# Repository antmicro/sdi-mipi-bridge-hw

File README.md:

# SDI to MIPI CSI-2 Bridge Hardware Design

Copyright (c) 2020-2023 [Antmicro](https://www.antmicro.com)

## Overview

This project contains open hardware KiCad design files for Antmicro's SDI to MIPI CSI-2 bridge.
This device enables connecting industrial and filmmaking cameras and video accessories to edge AI platforms which often include the MIPI CSI-2 interface.

The board includes an SDI input BNC connector and Antmicro's standard 50-pin FFC output connector (compatible with a range of our open hardware boards) exposing MIPI CSI-2 lanes as well as an I2C bus for configuration.

An additional SDI output (loopback) BNC connector is also available.

SDI signal conversion is implemented with a Semtech [GS2971A](https://www.semtech.com/products/broadcast-video/receivers-deserializers/gs2971a) deserializer which passes the parrallel 10-bit video data to the Lattice CrossLink [LIF-MD6000-6KMG80I](http://www.latticesemi.com/en/Products/FPGAandCPLD/CrossLink).
The CrossLink FPGA includes programmable logic and dedicated MIPI D-PHY transceivers.
It can be configured to accept parallel video data from the deserializer and transmit it over MIPI CSI-2 to the host platform.
SPI and I2C programming interfaces are exposed so the deserializer and the CrossLink FPGA can be configured from the host platform.

### Project structure

The main directory contains KiCad PCB project files, a LICENSE and README.
The remaining files are stored in the following directories:

* ``lib`` - contains the component libraries
* ``doc`` - contains board schematic in PDF
* ``img`` - contains graphics for this README

## Key Features

* Implements Single Link (3G-SDI) video conversion
* Supports SMPTE ST 425 (Level A and Level B), SMPTE ST 424, SMPTE ST 292, SMPTE ST 259-C and DVB-ASI as defined by the Semtec GS2971A specification
* Integrated loopback BNC connector for easy daisy-chaining with multiple SDI video accessories
* Audio de-embedder for 8 channels of 48kHz audio exposed on I2S 10 pin header
* Two 4-lane MIPI CSI-2 interfaces with up to 6 Gbps, each exposed on the 50 pin FFC connector.
* I2C configuration interface to handle CrossLink FPGA and SDI deserializer
* SPI interface for CrossLink configuration
* 12x DIP switches to initially configure the deserializer
* 2 LED indicators for user purposes

## Getting started

Please refer to the [SDI to MIPI CSI-2 bridge](https://github.com/antmicro/sdi-mipi-bridge) repository which aggregates the hardware design (this project), linux kernel sources, how-to documentation and reference HDL design for the CrossLink FPGA.

## License

This project is licensed under the [Apache-2.0](LICENSE) license.

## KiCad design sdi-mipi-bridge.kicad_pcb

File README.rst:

========================
SDI to MIPI CSI-2 bridge
========================

Copyright (c) 2020-2021 `Antmicro <https://www.antmicro.com>`_

.. figure:: img/sdi-mipi-bridge.jpg

Overview
========

This repository contains open hardware KiCad design files for Antmicro's SDI to MIPI CSI-2 bridge.
This device enables connecting industrial and filmmaking cameras and video accessories to edge AI platforms which often include the MIPI CSI-2 interface.

The board includes an SDI input BNC connector and Antmicro's standard 50-pin FFC output connector (compatible with a range of our open hardware boards) exposing MIPI CSI-2 lanes as well as an I2C bus for configuration.

An additional SDI output (loopback) BNC connector is also available.

SDI signal conversion is implemented with a `Semtech GS2971A <https://www.semtech.com/products/broadcast-video/receivers-deserializers/gs2971a>`_ deserializer which passes the parrallel 10-bit video data to the `Lattice CrossLink LIF-MD6000-6KMG80I <http://www.latticesemi.com/en/Products/FPGAandCPLD/CrossLink>`_.
The CrossLink FPGA includes programmable logic and dedicated MIPI D-PHY transceivers.
It can be configured to accept parallel video data from the deserializer and transmit it over MIPI CSI-2 to the host platform.
SPI and I2C programming interfaces are exposed so the deserializer and the CrossLink FPGA can be configured from the host platform.
Additionally, a set of DIP switches allows the user to easily pre-set the mode of operation of the deserializer.

Repository structure
--------------------

The main repository directory contains KiCad PCB project files, a LICENSE and README.
The remaining files are stored in the following directories:

* ``3d-model`` - contains a `mechanical model <3d-model/sdi-mipi-bridge.stl>`_ of the board in stl mesh format
* ``lib`` - contains the component libraries
* ``doc`` - contains selected files for device fabrication (schematic in PDF, BoM)
* ``img`` - contains graphics for this README

Key Features
============

* Implements Single Link (3G-SDI) video conversion
* Supports SMPTE ST 425 (Level A and Level B), SMPTE ST 424, SMPTE ST 292, SMPTE ST 259-C and DVB-ASI as defined by the Semtec GS2971A specification
* Integrated loopback BNC connector for easy daisy-chaining with multiple SDI video accessories
* Audio de-embedder for 8 channels of 48kHz audio exposed on I2S 10 pin header
* Two 4-lane MIPI CSI-2 interfaces with up to 6 Gbps, each exposed on the 50 pin FFC connector.
* I2C configuration interface to handle CrossLink FPGA and SDI deserializer
* SPI interface for CrossLink configuration
* 12x DIP switches to initially configure the deserializer
* 2 LED indicators for user purposes

Board dimensions
================

.. figure:: img/SDI_dimensions.png

Getting started
===============

The SDI-MIPI PCB can be manufactured and assembled from the provided design files.

The board can also be purchased preassembled from our partner `Capable Robot Components <https://capablerobot.com/products/sdi-mipi-bridge/>`_.

If you want to manufacture the board yourself, it is recommended to pick PCB manufacturing technology which guarantees impedance matching of the SDI and CSI high speed data lanes.
The board is powered with 3.3V DC through the 50-pin FFC host connector.
It is recommended to provide at least 1A of power supply.

Supported platforms
===================

The SDI-MIPI bridge is electrically compatible a range of processing platforms designed by Antmicro.
Most of them, such as the NVIDIA `Jetson Nano/Jetson Xavier NX baseboard <https://github.com/antmicro/jetson-nano-baseboard>`_ or the `TX2 Deep Learning Platform <https://github.com/antmicro/jetson-tx2-deep-learning-platform>`_ are available as OSHW designs.

Software support
================

Currently there are two tutorials available for preparing BSPs which integrate the SDI-MIPI Bridge for:

* Jetson Nano Baseboard with Jetson Xavier NX - see the `tutorial <sw_setup_l4t.rst>`_
* Rasbperry Pi CM4 module - see the `tutorial <sw_setup_rpi.rst>`_

If you need help to make the board work with other edge AI platforms or integrate the SDI interface into your own, dedicated device, Antmicro offers custom hardware and software engineering services - please reach out at contact@antmicro.com and let us know about your requirements.

License
=======

`Apache-2.0 <LICENSE>`_

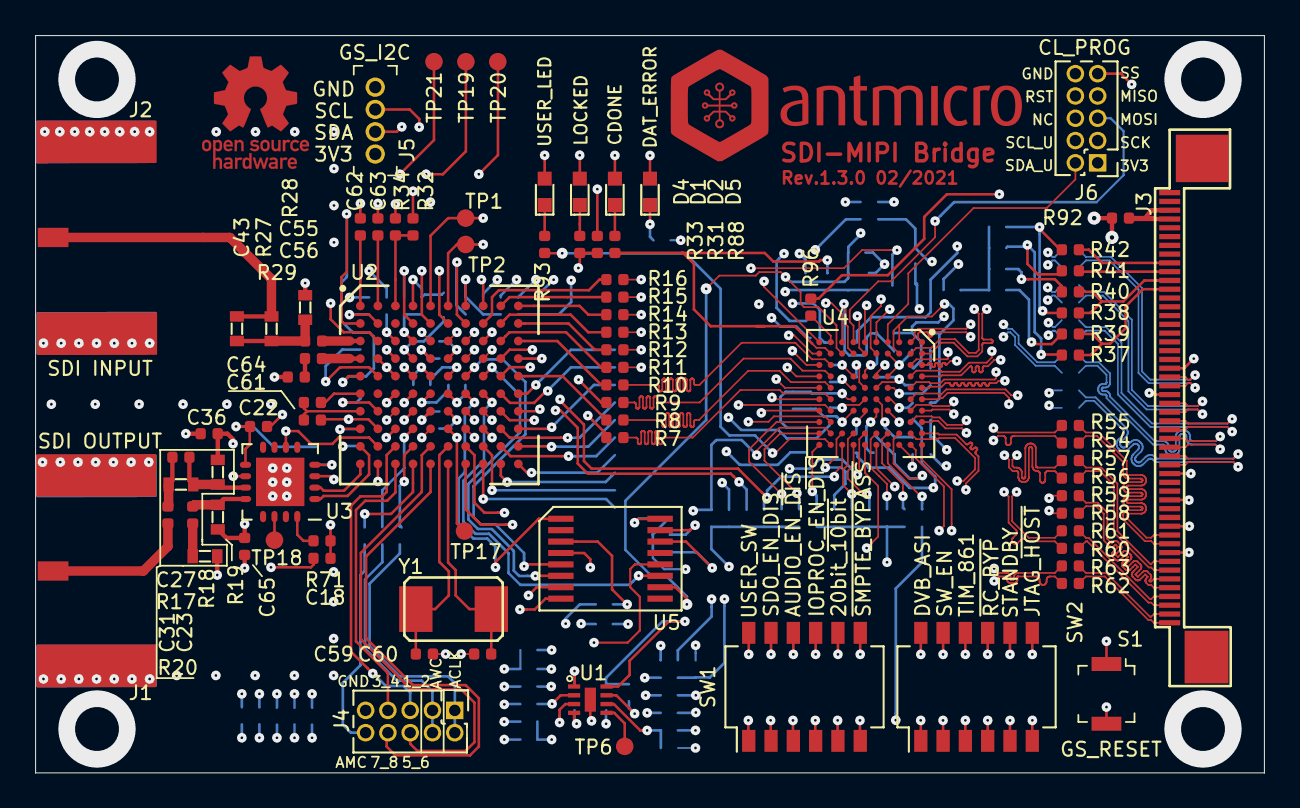
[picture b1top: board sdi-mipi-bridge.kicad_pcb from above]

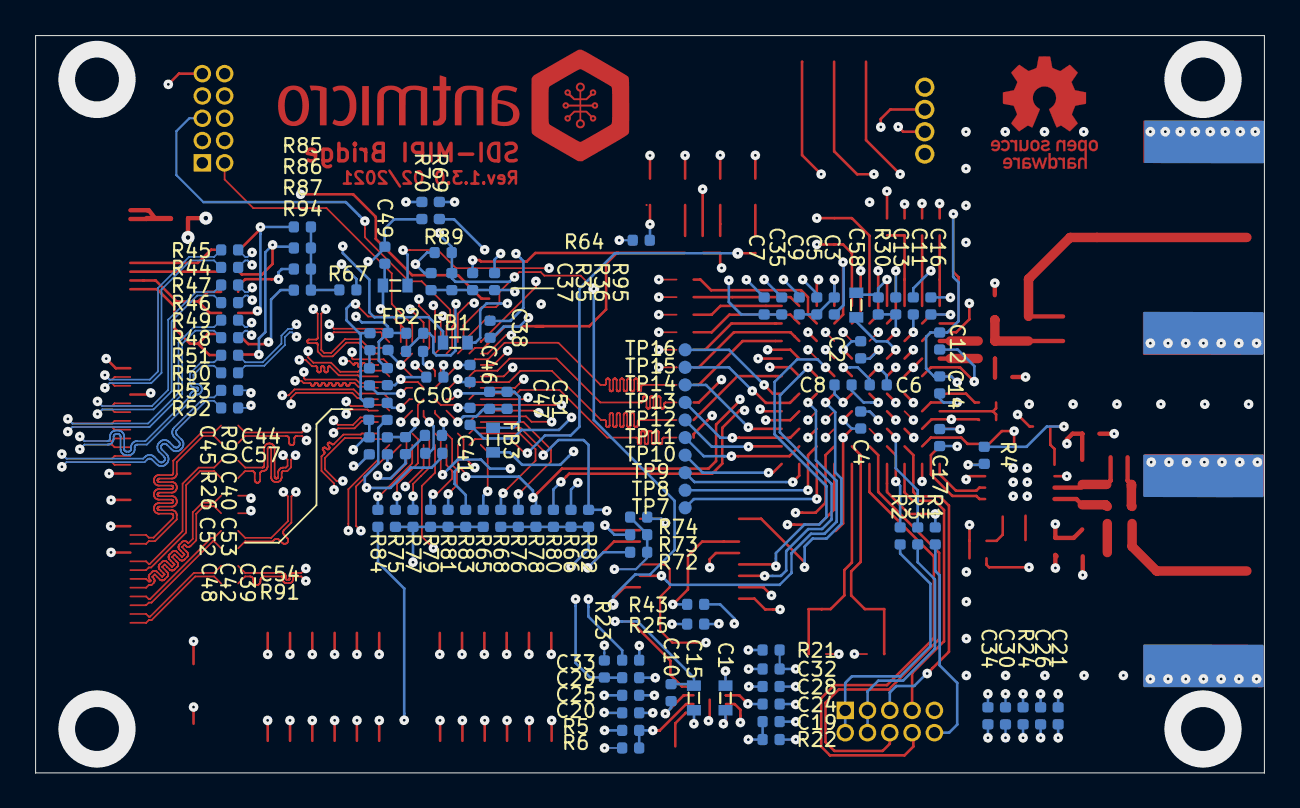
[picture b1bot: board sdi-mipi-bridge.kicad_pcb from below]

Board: 6 copper layers, 70.0 x 42.0 mm, 203 parts (116 on the bottom side), 174 nets.

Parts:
C1, C15: C_10u_0603; 0603-cap
C2, C3, C4, C5, C6, C7, C8, C9, C10, C11, C12, C13, C14, C16, C17, C18, C19, C20, C21, C22, C32, C33, C34, C36, C65: C_10n_0402; 0402-cap
C23, C31, C42, C52: C_4u7_0402; 0402-cap
C24, C25, C26, C28, C29, C30, C35, C45, C47, C55, C56, C62: C_1u_0402; 0402-cap
C27: C_5n6_0402; 0402-res
C37, C38: C_2u2_0402; 0402-cap
C39, C40, C41, C44, C46, C48, C49, C50, C51, C53, C54, C57: C_100n_0402_6V3; 0402-cap
C43: C_6n2_0603; 0603-res
C58: C_33u_0603; 0603-cap
C59, C60: C_16p_0402; 0402-res
C61, C64: C_470n_0402; 0402-cap
C63: C_47n_0402; 0402-cap
D1, D2, D4, D5: LG_L29K-G2J1-24-Z; LED_0603
FB1, FB2, FB3: BLM18PG121SH1D; 0603-res
J1, J2: 112740-13; BNC_Edge_Conn
J3: WE_68715014522_ONE-SIDE
J4, J6: GRPB052VWVN-RC; PinHeader_2x05_P1.27mm_Vertical
J5: GRPB041VWVN-RC; PinHeader_1x4_P1.27mm_Drill.7mm
N1: antmicro_logo; antmicro-logo_scaled_20mm
N2: oshw_logo; oshw-logo
R1, R2, R3: R_22R_0402; 0402-res
R4: R_750R_0402; 0402-res
R5, R6: R_120k_0402; 0402-res
R7, R8, R9, R10, R11, R12, R13, R14, R15, R16, R21, R22, R23, R24, R25, R26, R31, R32, R34, R37, R38, R39, R40, R41, R42, R43, R44, R45, R46, R47, R48, R49, R50, R51, R52, R53, R54, R55, R56, R57, R58, R59, R60, R61, R62, R63, R67, R69, R70, R71, R72, R73, R74, R89, R90, R91, R92: R_0R_0402; 0402-res
R17, R18, R19, R20, R27, R28: R_75R_0603; 0603-res
R29: R_37R4_0402; 0402-res
R30: R_105R_0402; 0402-res
R33, R64, R88, R93: R_100R_0402; 0402-res
R35, R36, R84, R95: R_4k7_0402; 0402-res
R65, R66, R68, R75, R76, R77, R78, R79, R80, R81, R82, R83: R_10k_0402; 0402-res
R85, R86, R87, R94: R_2k2_0402; 0402-res
R96: R_30R_0402; 0402-res
S1: B3U-1000P; Switch_Tactile_SMD_B3U-1000P
SW1, SW2: SW_DIP_x06; SW_SPST_6_Slide_MCDHN-06F-T-V_P1.27mm
TP1, TP2, TP6, TP17, TP18, TP19, TP20, TP21: TP_SMD1MM; Testpoint_smd_1mm
TP7, TP8, TP9, TP10, TP11, TP12, TP13, TP14, TP15, TP16: TP_SMD_0_75MM; Testpoint_smd_0_75mm
U1: MAX8902B; TDFN2x2
U2: GS2971A; BGA100_11x11mm
U3: GS2988; QFN-16_EP_4x4_Pitch0.65mm
U4: CrossLink_LIF-MD6000-6JMG80I; BGA-80pin_ckfBGA80_7.0x7.0mm
U5: SC18IS602BIPW; SC18IS602B
Y1: ABM7_27.000MH_D2Y_T; ABM7_OSC

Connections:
+1V2: C2.1, C4.1, C6.1, C8.1, C10.1, C15.1, C20.1, C25.1, C39.1, C42.1, C48.1, C52.1, FB2.1, FB3.1, R5.1, R23.1, U1.8, U2.D6, U2.E6, U2.F6, U2.G6, U4.E4, U4.E6
+3.3VA: C12.1, C14.1, C17.1, C28.1, C32.1, R21.2, R34.1, U2.B1, U2.E1, U2.H1
+3V3: C1.1, C19.1, C21.1, C24.1, C26.1, FB1.1, J5.1, J6.1, R21.1, R24.1, R25.1, R26.1, R43.1, R67.1, R92.2, U1.1, U1.3, U4.D5, U5.12
/20bit_~10bit: R76.2, SW1.8, U2.H7, U4.K8
/AGCN: C61.1, C64.2, U2.G1
/AGCP: C64.1, U2.F1
/AUDIO_MASTER_CLK: J4.10, R1.1
/AUDIO_OUTPUT_CH1_2: J4.5, U2.J3
/AUDIO_OUTPUT_CH3_4: J4.7, U2.K3
/AUDIO_OUTPUT_CH5_6: J4.6, U2.J5
/AUDIO_OUTPUT_CH7_8: J4.8, U2.K5
/AUDIO_SERIAL_BIT_CLK: J4.1, J4.2, R2.1
/AUDIO_WORD_CLK: J4.3, J4.4, R3.1
/Audio_EN_~DIS: R80.2, SW1.10, U2.H3, U4.J8
/CDONE: R36.1, R88.2, U4.J2
/CRESET_B: J6.8, R35.1, R89.2, U4.H2, U5.10
/D0: TP7.1, U2.K8
/D1: TP8.1, U2.J8
/D2: TP9.1, U2.K9
/D3: TP10.1, U2.K10
/D4: TP11.1, U2.J9
/D5: TP12.1, U2.J10
/D6: TP13.1, U2.H9
/D7: TP14.1, U2.H10
/D8: TP15.1, U2.F9
/D9: TP16.1, U2.F10
/D10: R7.2, U2.E9
/D11: R8.2, U2.E10
/D12: R9.2, U2.C8
/D13: R10.2, U2.C10
/D14: R11.2, U2.C9
/D15: R12.2, U2.B10
/D16: R13.2, U2.B9
/D17: R14.2, U2.A10
/D18: R15.2, U2.A9
/D19: R16.2, U2.B8
/DATA_ERRORb: R64.2, U2.C6, U4.E10
/DOUT10: R7.1, U4.J6
/DOUT11: R8.1, U4.J5
/DOUT12: R9.1, U4.J4
/DOUT13: R10.1, U4.J3
/DOUT14: R11.1, U4.E1
/DOUT15: R12.1, U4.K7
/DOUT16: R13.1, U4.K6
/DOUT17: R14.1, U4.K5
/DOUT18: R15.1, U4.K4
/DOUT19: R16.1, U4.K3
/DPHY0_CLK_N: R54.1, U4.A8
/DPHY0_CLK_P: R55.1, U4.B8
/DPHY0_D0_N: R56.1, U4.A7
/DPHY0_D0_P: R57.1, U4.B7
/DPHY0_D1_N: R58.1, U4.A9
/DPHY0_D1_P: R59.1, U4.B9
/DPHY0_D2_N: R60.1, U4.A6
/DPHY0_D2_P: R61.1, U4.B6
/DPHY0_D3_N: R62.1, U4.A10
/DPHY0_D3_P: R63.1, U4.B10
/DPHY1_CLK_N: R44.2, U4.A3
/DPHY1_CLK_P: R45.2, U4.B3
/DPHY1_D0_N: R46.2, U4.A2
/DPHY1_D0_P: R47.2, U4.B2
/DPHY1_D1_N: R48.2, U4.A4
/DPHY1_D1_P: R49.2, U4.B4
/DPHY1_D2_N: R50.2, U4.A1
/DPHY1_D2_P: R51.2, U4.B1
/DPHY1_D3_N: R52.2, U4.A5
/DPHY1_D3_P: R53.2, U4.B5
/DVB_ASI: R65.1, SW2.12, U2.G8, U4.K10
/F_DE: TP19.1, U2.B5, U4.F9
/GNDGPLL: C47.2, C51.2, R69.2, U4.G7
/GNDPLL_DPHY: C49.2, C53.2, R70.2, U4.D6
/H_HSYNC: TP1.1, U2.A5, U4.F1
/IOPROC_EN_~DIS: R78.2, SW1.9, U2.H8, U4.H10
/JTAG_~HOST: R75.1, SW2.7, U2.D8, U4.D9
/LB_CONT: R32.2, R34.2, U2.A3
/LF: C63.2, U2.A2
/LOCKED: R31.1, R33.2, TP20.1, U2.B6
/LOCKED_CL: R31.2, U4.E2
/MIPI0_CLK_N: J3.10, R54.2
/MIPI0_CLK_P: J3.11, R55.2
/MIPI0_D0_N: J3.7, R56.2
/MIPI0_D0_P: J3.8, R57.2
/MIPI0_D1_N: J3.5, R58.2
/MIPI0_D1_P: J3.6, R59.2
/MIPI0_D2_N: J3.3, R60.2
/MIPI0_D2_P: J3.4, R61.2
/MIPI0_D3_N: J3.1, R62.2
/MIPI0_D3_P: J3.2, R63.2
/MIPI1_CLK_N: J3.28, R44.1
/MIPI1_CLK_P: J3.29, R45.1
/MIPI1_D0_N: J3.25, R46.1
/MIPI1_D0_P: J3.26, R47.1
/MIPI1_D1_N: J3.23, R48.1
/MIPI1_D1_P: J3.24, R49.1
/MIPI1_D2_N: J3.21, R50.1
/MIPI1_D2_P: J3.22, R51.1
/MIPI1_D3_N: J3.19, R52.1
/MIPI1_D3_P: J3.20, R53.1
/MISO: J6.7, U4.K1
/MOSI: J6.5, U4.G1
/PCLK: U2.A8, U4.J7
/RST_TRST: R84.2, S1.1, U2.C7, U4.D10
/SCL1: J3.40, R38.1, R40.1
/SCL2: J3.42, R42.1
/SCLK_TCK: U2.F8, U5.11
/SCL_GS: J5.3, R40.2, R87.2, U5.8
/SDA1: J3.39, R37.1, R39.1
/SDA2: J3.41, R41.1
/SDA_GS: J5.2, R39.2, R94.2, U5.7
/SDIN_TDI: U2.E8, U5.6
/SDI_N: C56.1, U2.D1
/SDI_P: C55.1, U2.C1
/SDOUT_TDO: U2.E7, U5.5
/SDO_EN_DIS: R66.2, SW1.11, U2.J2, U3.6
/SDO_N: U2.K1, U3.2
/SDO_P: U2.J1, U3.1
/SPI_SCK(SDA): J6.3, R37.2, R41.2, R86.2, R96.1
/SPI_SS(SCL): J6.9, R38.2, R42.2, R85.2, R95.1, U4.H1
/STANDBY: R77.1, SW2.8, U2.K2, U4.E9
/SW_EN: R83.1, SW2.11, U2.D7, U4.H9
/TIM_861: R81.1, SW2.10, U2.H5, U4.G9
/USER_LED: R93.2, U4.J10
/USER_SCL: J6.4, U4.K2
/USER_SDA: J6.2, U4.D1
/USER_SW: R82.2, SW1.12, U4.J9
/VBG: C62.2, U2.A1
/V_VSYNC: TP2.1, U2.A6, U4.F2
/XTAL1: C60.1, U2.K6, Y1.2
/XTAL2: C59.1, U2.J6, Y1.1
/Y_1ANC: TP21.1, U2.C5, U4.F10
/~CS_TMS: U2.F7, U5.1
/~RC_BYP: R79.1, SW2.9, U2.G3, U4.G10
/~SMPTE_BYPASS: R68.2, SW1.7, U2.G7, U4.K9
GNDA: C11.2, C12.2, C13.2, C14.2, C16.2, C17.2, C18.2, C22.2, C28.2, C29.2, C30.2, C32.2, C33.2, C34.2, C36.1, C58.2, C61.2, C62.1, C63.1, C65.1, J1.1, J2.1, J4.9, R20.1, R22.2, R28.2, R29.2, R32.1, R65.2, R66.1, R68.1, R75.2, R76.1, R77.2, R78.1, R79.2, R80.1, R81.2, R82.1, R83.2, S1.2, U2.B4, U2.C2, U2.D2, U2.D3, U2.D4, U2.E2, U2.E3, U2.E4, U2.F3, U2.F4, U2.G2, U2.H2, U3.3, U3.10, U3.17
GNDREF: C1.2, C2.2, C3.2, C4.2, C5.2, C6.2, C7.2, C8.2, C9.2, C15.2, C19.2, C20.2, C21.2, C24.2, C25.2, C26.2, C35.2, C37.2, C38.2, C39.2, C40.2, C41.2, C42.2, C44.2, C45.2, C46.2, C48.2, C50.2, C52.2, C54.2, C57.2, C59.2, C60.2, D1.2, D2.2, D4.2, D5.2, J3.9, J3.12, J3.15, J3.18, J3.27, J3.30, J5.4, J6.10, R6.2, R22.1, R69.1, R70.1, R72.1, R73.1, R74.1, R89.1, U1.2, U1.4, U1.~, U2.B7, U2.D5, U2.D9, U2.E5, U2.F5, U2.G4, U2.G5, U2.G9, U2.J7, U4.C1, U4.C2, U4.C9, U4.C10, U4.E5, U4.G2, U4.G5, U5.4
IO_VDD: C3.1, C5.1, C7.1, C9.1, C35.1, R25.2, R84.1, SW1.1, SW1.2, SW1.3, SW1.4, SW1.5, SW1.6, SW2.1, SW2.2, SW2.3, SW2.4, SW2.5, SW2.6, U2.A7, U2.D10, U2.G10, U2.K7
unnamed: C10.2, U1.7
unnamed: C23.1, R19.1, U3.12
unnamed: C23.2, R20.2
unnamed: C27.1, C31.2, R17.2
unnamed: C27.2, R17.1, R18.1, U3.11
unnamed: C31.1, J1.2
unnamed: C43.1, C55.2, R27.1, R28.1
unnamed: C43.2, J2.2, R27.2
unnamed: C45.1, R26.2
unnamed: C56.2, R29.1
unnamed: D1.1, R33.1
unnamed: D2.1, R88.1
unnamed: D4.1, R93.1
unnamed: D5.1, R64.1
unnamed: J3.47, J3.48, R92.1
unnamed: R1.2, U2.K4
unnamed: R2.2, U2.J4
unnamed: R3.2, U2.H4
unnamed: R4.2, U3.4
unnamed: R5.2, R6.1, U1.6
unnamed: R43.2, U5.3
unnamed: R67.2, R85.1, R86.1, R87.1, R94.1
unnamed: R71.2, U3.16
unnamed: R72.2, U5.14
unnamed: R73.2, U5.15
unnamed: R74.2, U5.16
unnamed: R90.2, U4.D2, U4.D4
unnamed: R91.2, U4.D7, U4.E7
unnamed: R96.2, U4.J1
unnamed: TP6.1, U1.5
unnamed: TP17.1, U2.H6
unnamed: TP18.1, U3.14
VCCA_DPHY: C38.1, C40.1, C44.1, C49.1, C53.1, FB2.2, R90.1, R91.1
VCCGPLL: C47.1, C51.1, FB3.2, U4.G6
VCC_IO: C37.1, C41.1, C46.1, C50.1, C54.1, C57.1, FB1.2, R35.2, R36.2, R95.2, U4.F4, U4.F5, U4.F6, U4.F7, U4.G4
VCO_VDD: C58.1, R30.2, U2.A4
VDD: C18.1, C22.1, C30.1, C34.1, C36.2, C65.2, R4.1, R18.2, R19.2, R24.2, R71.1, U3.9
VPP: C11.1, C13.1, C16.1, C29.1, C33.1, R23.2, R30.1, U2.B2, U2.C3, U2.C4

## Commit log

2019-11-18 Add schematic sheet
2019-11-18 Add descriptions
2020-06-25 Add .gitignore
2020-06-25 Add LICENSE
2020-06-25 Update directory structure
2020-06-25 Add todos
2020-06-25 Add cache files to .gitignore
2020-06-25 Expose DPHY1 at FFC connector
2020-06-25 Fix inner layer clearance and tracks width
2020-06-25 Clean up designators
2020-06-25 Add CrossLink to schematic
    Also changed:
    -add 50-pin mipi connector
    -remove b2b connector
    -remove jumpers and conect signals to fpga
    -remove audio testpats and connect signals to fpga
2020-06-25 Add routing on 6 layers
2020-06-25 Add I2S connector and GND planes
2020-06-25 Clean Designators
2020-06-25 Initial component placement and outline definition
2020-06-25 Add complete routing
2020-06-25 Schematic changes after design review
2020-06-25 Complete pcb routing
2020-06-25 Arrange pcb components and add jumpers and logo
2020-06-25 Update component placement
2020-06-25 Remove stub at F2
2020-06-25 Initial routing -WIP
2020-06-25 Add updated schematic
2020-06-25 Schematic cleanup
2020-06-25 Fix inner layer clearance
2020-06-25 Add routing - WIP
2020-06-25 Add CrossLink power filtering
2020-06-25 Tune differential pair lengths
2020-06-25 Add OSHW logo and fix CS pin
    There are following changes made:
    -Disconnect CS pin from dip switch
    -Replace one user led with user switch
    -Remove leftovers form previous revision
    -Update date and revision
2020-06-25 Update revision info on PCB
2020-06-25 Add LED indicators and swap pin numbers of BNC connectors
2020-06-25 README updates
2020-06-25 Define release 1.0.0
2020-06-25 Rework the layout of SDI input and output path
2020-06-25 Tune parallel signal length
2020-06-25 Cleanup before release
2020-06-25 Switch In1.Cu with In4.Cu and add via fence
2020-06-25 Add several components to simplify the debugging process
    -Add DIP switches for GS external configuration
    -Make PCB a bit widther
    -Move monting holes to the board sides
    -Move power supply components
    -Add Programming connectors
    -Expose all audio pins at header
2020-06-25 Fix minor footprint bug
2020-06-25 Update photo
2020-06-25 Fixed designators orientation
2020-06-25 Schematic updates
2020-06-25 Add infill to schematic symbols
2020-06-25 Library updates
2020-06-25 Minor fixes added to layout
2020-06-25 Update naming convention
2020-06-25 Update MPNs
2020-07-02 Update 3.3V symbol
2020-07-02 Fixed 3V3 reference
2020-07-02 Added missing MPNs
2020-07-02 Add PCB documentation
2020-07-16 Review README
2020-07-16 Add link to model
2020-08-19 Unify GS2971A MPN in README
2020-08-19 Update the GS2971A markings in the library
2020-08-19 Add stackup table to the PCB fab layer
2020-08-20 Update 3D model of the BNC connector
2020-08-20 Update 3D model of the board
2020-11-29 Changed MFG and MPN for some parts to ease sourcing
2020-11-29 Chnage from 12G to 6G BNC connectors
2020-11-30 Change C37 from 2n2 to 2u2
2020-11-30 Update schematic PDF
2020-12-03 Connect PCLK to J7 pin
2020-12-03 Replace DOUT10 and DOUT11 resistors with test pads
2020-12-03 Add DNP field to SDA_CL resistors
2020-12-03 Add second user LED
2020-12-03 Add changes to PCB
    Connect PCLK signal to J7 pin of FPGA
    Replace DOUT10 and DOUT11 resistors with test pads
    Add second user LED indicator
2020-12-03 Update PDF schematic
2020-12-04 Change data pins connection
2020-12-04 Change data pins routing
2020-12-04 Minor fix, regenerate schematics
2020-12-04 Re-mapped Dx signal names between the deserializer and CrossLink
2020-12-04 Update PCB, DRC clean
2020-12-16 Add 0R resistor on 3.3v input to allow FFC to be disconnected from net
2020-12-18 Increase 3.3v trace width, added 2nd via, increased via diameter
2020-12-18 Change font size for R92
2020-12-18 Change RST pullup from 2k2 to 4k7 and note I2C pull-ups as DNP
2021-01-29 Update LICENSE
2021-02-10 Bump release to 1.3.0
2021-02-10 Connect CRESET_B to GPIO2 from U5
2021-02-10 Connect configuration I2C from U4 to J3
2021-02-10 Reuse R37,R38 to reconnect configuration I2C
2021-02-10 Update layout DRC-clean
2021-02-10 Update STANDBY label near SW2
2021-02-10 Update DNP attributes
2021-02-10 Add PDF schematics
2021-03-22 Add BSP setup guide
2021-03-22 Add scripts directory
2021-04-05 Review README once more
2021-04-05 Fix link
2021-04-13 Update sw_setup.rst
    `make modules_install` fails due to permission issues in the unpacked rootfs.
    If run with sudo, the current kernel config is ignored and a prompt is entered. Additional steps have been added to change the lib/modules and lib/firmware directories to be owned by the current user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
2021-04-20 Add colons
2021-06-24 Notes added by 'git notes add'
2022-08-12 Add Raspberry Pi setup readme
2023-02-17 Add switches configuration to readme
2023-02-17 Add comment on the default configuration of the DIP switches
2023-02-17 README: mention supported platforms as a bullet list
2023-02-17 Fix typo
2023-02-17 Remove redundant quotes
2023-02-27 Ported to KiCAD 6
2023-02-27 Tidy up the schematic
2023-02-27 Improved RST_TRST circuit
2023-02-27 Fixed DIP switches shorting FPGA to IO_VDD
2023-03-01 Removed DIP switches and improved RST_TRST circuitry
2023-03-01 Ported DIP switch and reset changes to the PCB
2023-03-01 Changed dnp components to virtual
2023-03-01 Copied stackup from user drawings to KiCAD settings
2023-03-01 Readded mounting holes
2023-03-01 Tidy up the silkscreen
2023-03-01 Unified configuration naming and changed DATA_ERROR name polarity
2023-03-01 Added PCB SHA and few silkscreen tweaks
2023-06-05 Cleanup
2023-06-05 Update README to MD
2023-06-05 Update PCB marking string
2023-06-05 Update link
2023-06-06 Add PCB SHA marking
2023-06-07 Fix DRC violations
2023-06-12 Remove 0R resistors from the fast signal lanes
2023-06-13 Redraw filled zones
2023-06-13 Resolve DRC
2023-06-13 Bump project revision to 1.3.1
2023-06-13 Update silkscreen markings around J4
2023-06-13 Resolve DRC issues related to silkscreen
2023-06-13 Leave only one PCB SHA marking
2023-07-17 Generated schematic and assembly drawings
2023-07-17 Applied globlib
2023-07-17 Standardized SDI input and output sections
2023-07-17 Started standardizing the schematic
2023-07-18 Continued schematic standarization
2023-07-18 Finished schematic migration
2023-07-18 Started migrating the PCB
2023-07-19 Imported schematic changes to the PCB and placed components
2023-07-19 Finished migrating the PCB silkscreen
2023-07-20 Cleared DRC warnings
2023-07-20 Applied loclib
2023-07-26 Added missing layers in PCB stackup
2023-08-09 [#47298] Bump revision to 1.3.2
2023-08-09 [#47298] Add exclusion to ERC
    Label 'RST' is not connected to anything on main branch too
2023-08-09 [#47298] Add exclusion to ERC
2023-08-09 [#47298] Fix ERC errors
2023-08-09 [#47298] Fix ERC
2023-08-09 [#47298] Fix most of the ERC errors
2023-08-09 [#47298] Fix MAX8902B symbol
    Change pin 8 type from output to power output
2023-08-09 [#47298] Add ERC exclusion to power symbols
2023-08-09 [#47298] Fix DNP
2023-08-09 [#47298] Add title and company name to PCB drawing
2023-08-09 [#47298] Fix unconnected pins in symbols
    Change unconnected pins of GS2989 and GS2971A from stacked to unstacked
2023-08-09 [#47298] Resolve ERC errors. ERC clean. DRC clean
2023-08-09 [#47298] Bump revision to 1.3.3
2023-08-22 [#48149] Change GS297 footprint for footprint with markings
2023-08-23 [#48149] Update GS297 symbol, update loclib
2023-09-11 Update default configuration resistors
2023-09-11 Bump revision to 1.3.4
2023-09-13 Add OHP assets
2023-10-12 50070 fix drc
2023-11-09 Update assets
2024-02-26 [#55723] Fix 2199SB-10G-301523
2024-02-26 [#55723] Fix MC-HVT1-S04-G
2024-02-26 [#55723] Fix MAX8902B
2024-02-26 [#55723] Fix LIF-MD6000-6JMG80I
2024-02-26 [#55723] Updated fixed components on pcb
2024-02-26 [#55723] Run loclib
2024-02-27 [#55723] Update assets
2024-02-29 [#55723] Fix Conn_BNC_031-70526-21
2024-04-02 Fix symbols/footprint coordinates
